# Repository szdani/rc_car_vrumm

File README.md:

## Project Structure
- `pc_client`: Python based GUI for debugging (running on Linux, tested on Ubuntu18.04)
- `pcb`: Circuit and layout design.
- `freertos_car_driver`: Embedded software running on the car's hardware.
- `3D_model`: Blender based 3D model for the cat's frame.

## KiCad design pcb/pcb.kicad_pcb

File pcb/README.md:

## PCB & Circuit Design
For circuit and layout design KiCad 5.1.7 was used.

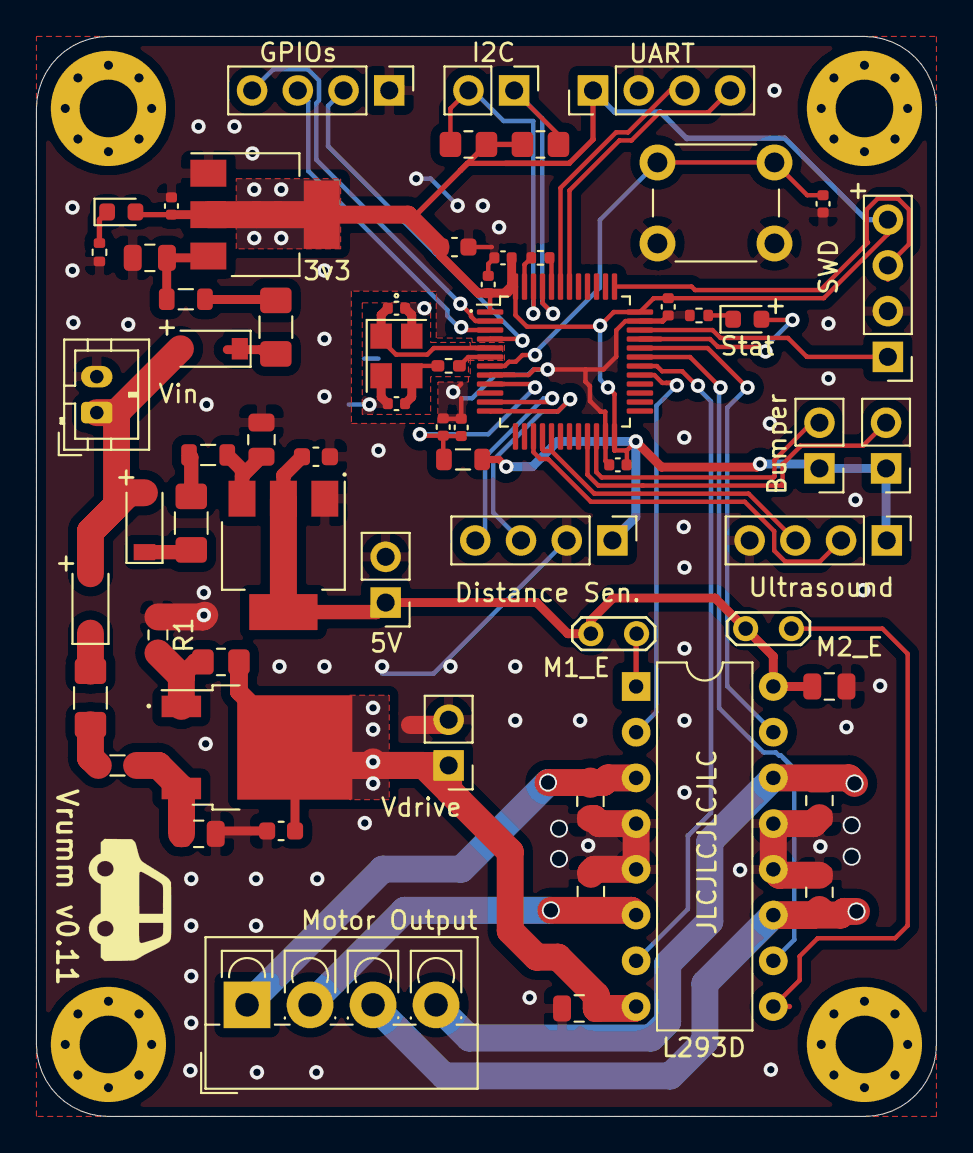
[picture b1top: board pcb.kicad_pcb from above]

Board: 2 copper layers, 50.0 x 60.0 mm, 67 parts (0 on the bottom side), 49 nets.

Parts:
C1, C3, C5: 0.1uF; C_0805_2012Metric
C2: 1uF; C_0603_1608Metric
C4, C7, C8, C9, C10, C15: 10uF; C_0805_2012Metric
C6: 10uF; C_0603_1608Metric
C13, C18, C19, C20, C21: 100nF; C_0402_1005Metric
C14: 10nF; C_0402_1005Metric
C16: 10uF; C_0402_1005Metric
C17: 4.7uF; C_0603_1608Metric
CL1, CL2: 12pF; C_0402_1005Metric
CL3: 0.1uF; C_0402_1005Metric
D1, D2, D3: B5819W; D_SOD-123
D4, D5: Red LED; LED_0603_1608Metric
F1, F2, F3: 500mA; Fuse_1206_3216Metric_Pad1.42x1.75mm_HandSolder
FB1, FB2, FB3, FB4: 100 @ 100 MHz; L_0805_2012Metric
H1, H2, H3, H4: MountingHole; MountingHole_3.2mm_M3_Pad_Via
I2C1: J0; PinHeader_1x02_P2.54mm_Vertical
J1: Battery Input; JST_PH_B2B-PH-K_1x02_P2.00mm_Vertical
J2: Vdrive output; PinHeader_1x02_P2.54mm_Vertical
J3: 5V output; PinHeader_1x02_P2.54mm_Vertical
J4: MOTOR_OUT; TerminalBlock_4Ucon_1x04_P3.50mm_Vertical
J5: US_SENSOR; PinHeader_1x04_P2.54mm_Vertical
J6: BUMPER_SENSOR_FRONT; PinHeader_1x02_P2.54mm_Vertical
J7: BUMPER_SENSOR_BACK; PinHeader_1x02_P2.54mm_Vertical
J8: BT_USART; PinHeader_1x04_P2.54mm_Vertical
J9: GPIO; PinHeader_1x04_P2.54mm_Vertical
J10: Conn_01x04_Male; PinHeader_1x04_P2.54mm_Vertical
J11: STM32_SWD; PinHeader_1x04_P2.54mm_Vertical
JP1: M_JP_1; TestPoint_2Pads_Pitch2.54mm_Drill0.8mm
JP2: M_JP_2; TestPoint_2Pads_Pitch2.54mm_Drill0.8mm
R1: 910; R_0603_1608Metric_Pad0.98x0.95mm_HandSolder
R2: 240; R_0805_2012Metric_Pad1.20x1.40mm_HandSolder
R3, R8: 2k2; R_0402_1005Metric
R4: 220; R_0402_1005Metric_Pad0.72x0.64mm_HandSolder
R5, R6: 2k2; R_0805_2012Metric_Pad1.20x1.40mm_HandSolder
R7: 10k; R_0402_1005Metric
SW1: SW_Push; SW_PUSH_6mm_H4.3mm
U1: LM317_TO-252; TO-252-2
U2: L293D; DIP-16_W7.62mm
U3: AMS1117-5.0; SOT-223-3_TabPin2
U4: AMS1117-3.3; SOT-223-3_TabPin2
U5: STM32F103C8T6; LQFP-48_7x7mm_P0.5mm
Y1: X322516MLB4SI; Crystal_SMD_3225-4Pin_3.2x2.5mm

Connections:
+3.3VA: C13.1, C14.1, FB2.1, U5.9
+3V3: C16.1, C17.1, C18.1, C19.1, C20.1, C21.1, D5.2, FB2.2, J5.1, J6.1, J7.1, J8.1, J10.1, J11.4, R5.1, R6.1, U4.2, U5.1, U5.24, U5.36, U5.48
+5V: C3.1, C6.1, J3.1, JP1.1, JP2.1, U2.16, U3.2
BUMPER_BACK: J7.2, U5.22
BUMPER_FRONT: J6.2, U5.21
GND: C1.2, C2.2, C3.2, C4.2, C5.2, C6.2, C7.1, C8.2, C9.1, C10.2, C13.2, C14.2, C15.2, C16.2, C17.2, C18.2, C19.2, C20.2, C21.2, CL1.2, CL2.2, CL3.1, J1.2, J2.2, J3.2, J5.4, J8.2, J9.1, J10.2, J11.2, R1.1, R3.2, R7.2, R8.2, SW1.2, U2.4, U2.5, U2.12, U2.13, U3.1, U4.1, U5.8, U5.23, U5.35, U5.47, Y1.2, Y1.4
GPIO_13: J9.4, U5.2
GPIO_14: J9.3, U5.3
GPIO_15: J9.2, U5.4
HSE_IN: CL1.1, U5.5, Y1.1
HSE_OUT: R4.1, U5.6
I2C_SCL: I2C1.1, R5.2, U5.45
I2C_SDA: I2C1.2, R6.2, U5.46
MOTOR1_CH1: U2.2, U5.29
MOTOR1_CH2: U2.7, U5.30
MOTOR2_CH1: U2.10, U5.31
MOTOR2_CH2: U2.15, U5.32
NRST: CL3.2, SW1.1, U5.7
unnamed: C1.1, FB4.1, U1.3
unnamed: C4.1, FB1.1, U3.3
unnamed: C7.2, J4.1, U2.3
unnamed: C8.1, J4.3, U2.11
unnamed: C9.2, J4.2, U2.6
unnamed: C10.1, J4.4, U2.14
unnamed: C15.1, FB3.1, U4.3
unnamed: CL2.1, R4.2, Y1.3
unnamed: D1.1, F1.1
unnamed: D2.1, F3.1
unnamed: D3.1, F2.1
unnamed: D4.1, R8.1
unnamed: D4.2, U5.33
unnamed: D5.1, R3.1
unnamed: F1.2, FB1.2
unnamed: F2.2, FB3.2
unnamed: F3.2, FB4.2
unnamed: JP1.2, U2.1
unnamed: JP2.2, U2.9
unnamed: R1.2, R2.2, U1.1
unnamed: R7.1, U5.44
SYS_SWCLK: J11.3, U5.37
SYS_SWDIO: J11.1, U5.34
USART_RX: J8.3, U5.43
USART_TX: J8.4, U5.42
US_ECHO: J5.3, U5.16, U5.17
US_TRIGGER: J5.2, U5.15
VCC: D1.2, D2.2, D3.2, J1.1
Vdrive: C2.1, C5.1, J2.1, R2.1, U1.2, U2.8
WHEEL_SENSOR_L: J10.4, U5.11
WHEEL_SENSOR_R: J10.3, U5.12

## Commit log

2020-11-03 Motor Driver Circuit & PCB Design
2020-11-03 PC Debug client GUI & updated BT class
2020-11-03 python 3 requirements
2020-11-03 3D Model
2020-11-19 FreeRTOS initial commit
2020-11-19 3D Model Frame v1.13
2020-11-19 PCB files for KiCad
2020-11-19 gitignore update & README update with freertos dir
2020-11-19 Remove unused BT control class
2020-11-19 Linux client: threading in BT, handling program exit
2020-11-19 Update issue templates
2020-12-19 SWD fix on pcb
2020-12-19 PCB: voltage divider on motor power
2020-12-19 pcb versioning on silk layer, 5v track width
2020-12-20 Vcc resistor network reverted, heatsinks to voltage regulators
2020-12-20 rendered pcb image
2022-06-22 Bump numpy from 1.18.1 to 1.22.0 in /pc_client
    Bumps [numpy](https://github.com/numpy/numpy) from 1.18.1 to 1.22.0.
    - [Release notes](https://github.com/numpy/numpy/releases)
    - [Changelog](https://github.com/numpy/numpy/blob/main/doc/HOWTO_RELEASE.rst)
    - [Commits](https://github.com/numpy/numpy/compare/v1.18.1...v1.22.0)
    ---
    updated-dependencies:
